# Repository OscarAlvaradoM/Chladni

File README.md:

Proyecto realizado para el congreso nacional de Física 2019.

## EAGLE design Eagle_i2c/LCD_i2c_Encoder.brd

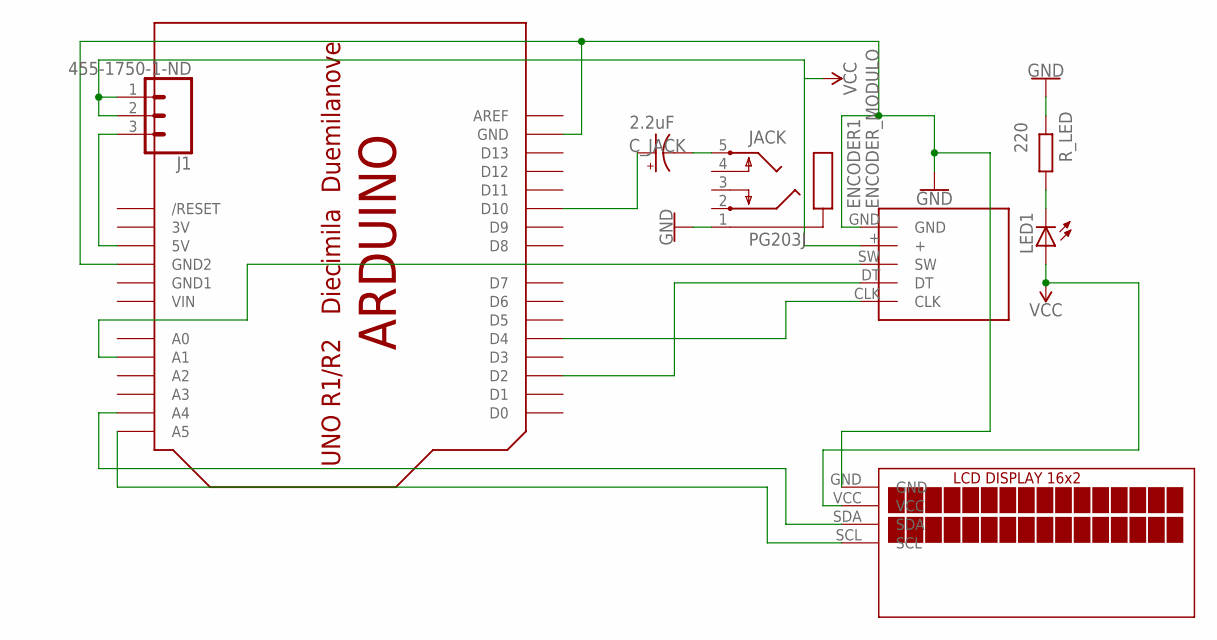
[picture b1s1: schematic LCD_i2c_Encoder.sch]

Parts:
C_JACK: CPOL-USE2,5-6E; E2,5-6E
ENCODER1: ENCODER_MODULO
J1: 455-1750-1-ND; 1X03
JACK: PG203J
LCD1: LCDI2C; TUXGR_16X2_R2
LED1: LED5MM
R_LED: R-EU_0204/7; 0204/7
U$1: ARDUINOUNO; ARDUINO

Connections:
3V: U$1.3V
GND: ENCODER1.GND, JACK.1, LCD1.GND, R_LED.2, U$1.GND, U$1.GND2
GND1: U$1.GND1
unnamed: C_JACK.+, U$1.D10
unnamed: ENCODER1.SW, U$1.A1
unnamed: LED1.K (C), R_LED.1
unnamed: J1.3, U$1.5V
unnamed: C_JACK.-, JACK.5
unnamed: LCD1.SDA, U$1.A4
unnamed: LCD1.SCL, U$1.A5
unnamed: ENCODER1.CLK, U$1.D4
unnamed: ENCODER1.DT, U$1.D2
VCC: ENCODER1.+, J1.1, J1.2, LCD1.VCC, LED1.A
VIN: U$1.VIN

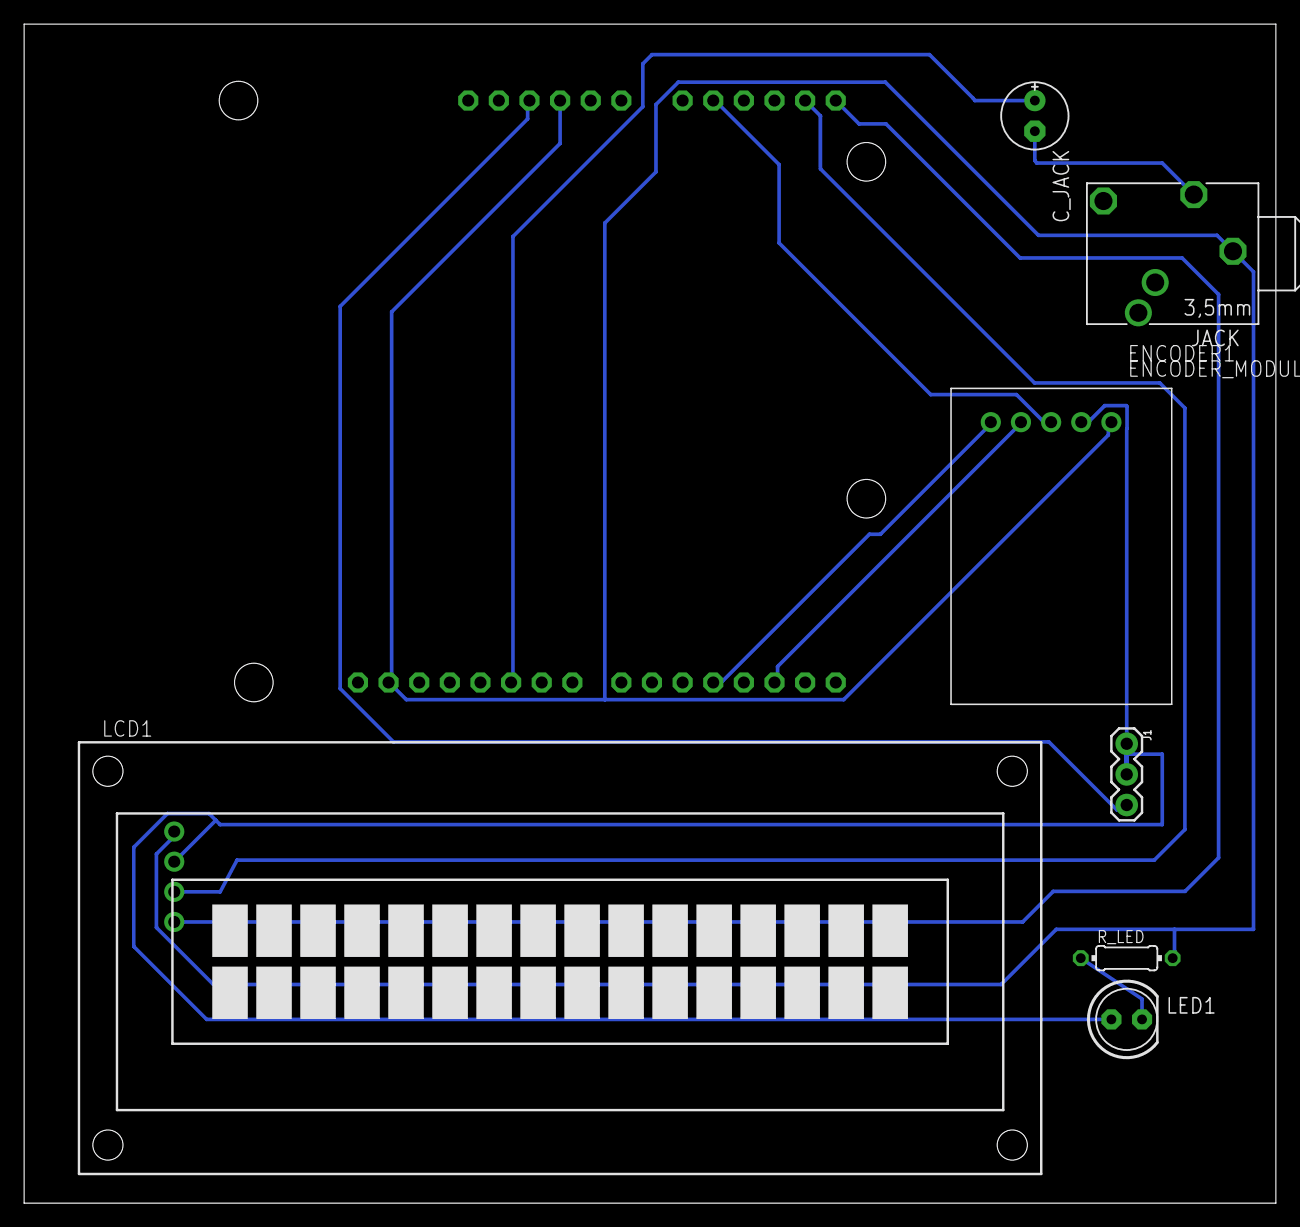
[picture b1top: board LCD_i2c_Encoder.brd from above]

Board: 2 copper layers, 103.8 x 97.8 mm, 8 parts (0 on the bottom side), 11 nets.

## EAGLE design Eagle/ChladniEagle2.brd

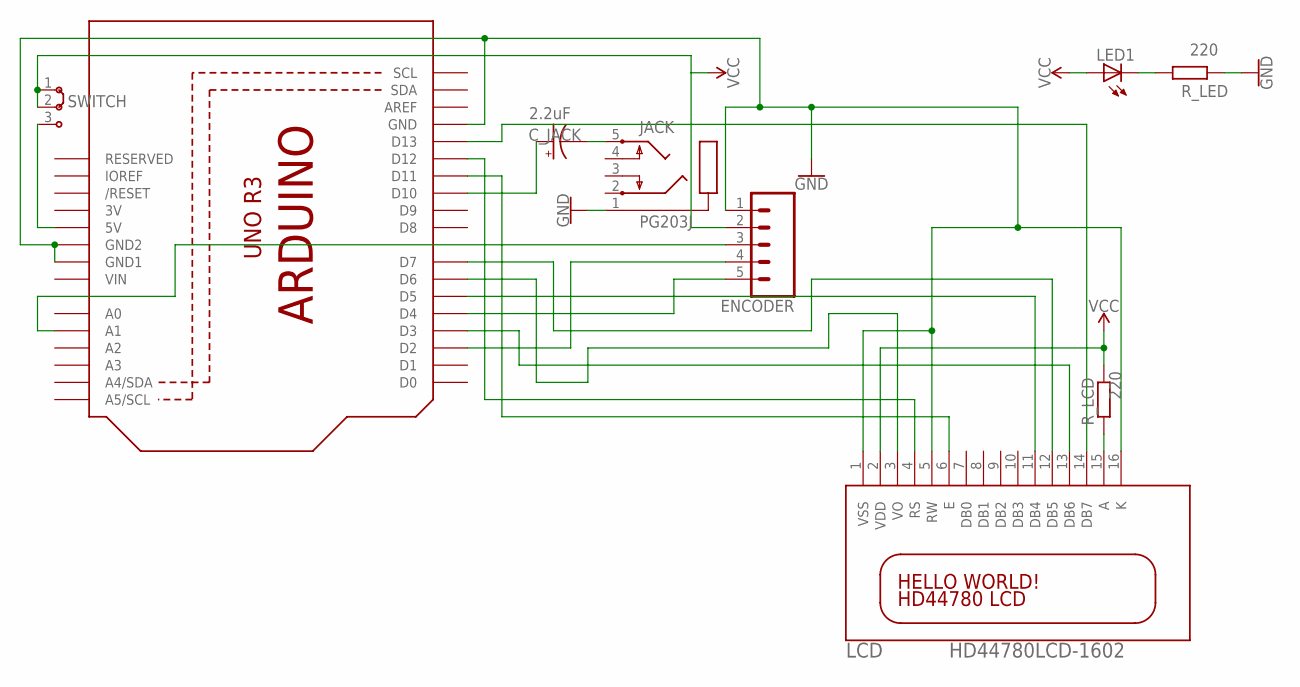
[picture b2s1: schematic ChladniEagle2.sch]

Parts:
C_JACK: CPOL-USE2,5-6E; E2,5-6E
ENCODER: CONN_05NO_SILK; 1X05_NO_SILK
JACK: PG203J
LCD: HD44780LCD-1602; LCD1602
LED1: LED5MM
R_LCD: R-EU_0204/7; 0204/7
R_LED: R-EU_0204/7; 0204/7
SWITCH: J2X2MM; 04C
U1: ARDUINOR3-BPLACE

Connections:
3V: U1.3V
GND: ENCODER.1, JACK.1, LCD.1 (VSS), LCD.5 (RW), LCD.16 (K), R_LED.2, U1.GND, U1.GND1, U1.GND2
unnamed: C_JACK.+, U1.D10
unnamed: ENCODER.3, U1.A1
unnamed: LED1.K (C), R_LED.1
unnamed: SWITCH.3, U1.5V
unnamed: C_JACK.-, JACK.5
unnamed: LCD.15 (A), R_LCD.1
unnamed: LCD.14 (DB7), U1.D13
unnamed: LCD.13 (DB6), U1.D3
unnamed: LCD.12 (DB5), U1.D7
unnamed: LCD.11 (DB4), U1.D5
unnamed: LCD.6 (E), U1.D11
unnamed: LCD.4 (RS), U1.D12
unnamed: LCD.3 (VO), U1.D6
unnamed: ENCODER.5, U1.D4
unnamed: ENCODER.4, U1.D2
VCC: ENCODER.2, LCD.2 (VDD), LED1.A, R_LCD.2, SWITCH.1, SWITCH.2
VIN: U1.VIN

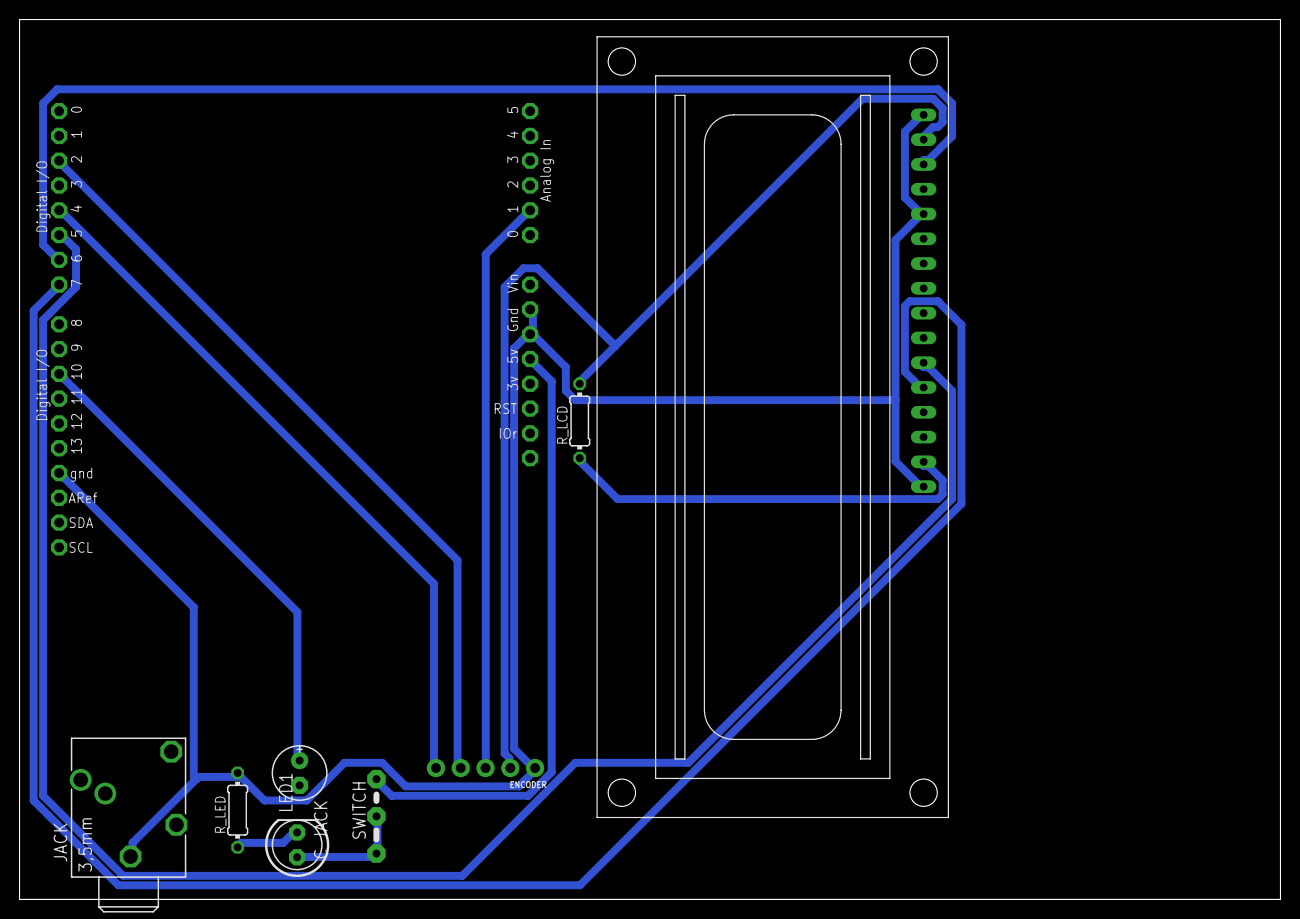
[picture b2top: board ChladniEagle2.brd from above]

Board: 2 copper layers, 129.2 x 90.2 mm, 9 parts (0 on the bottom side), 17 nets.

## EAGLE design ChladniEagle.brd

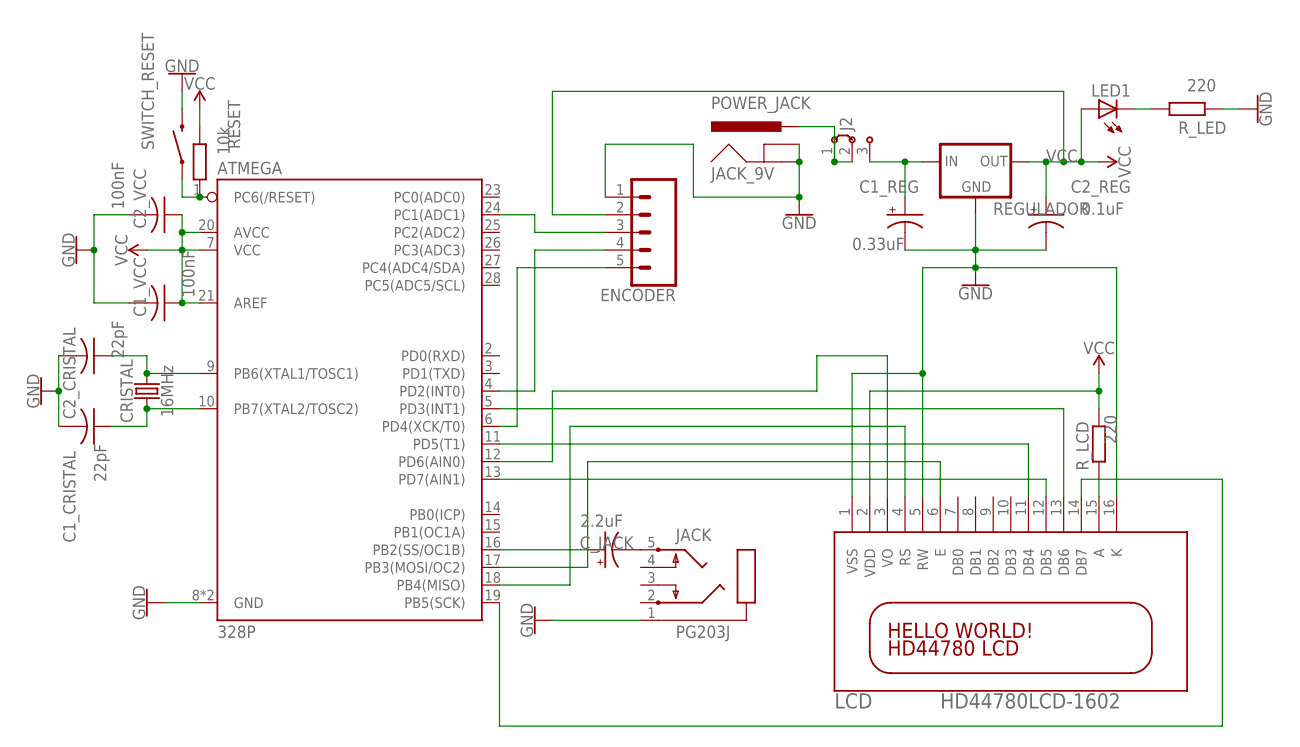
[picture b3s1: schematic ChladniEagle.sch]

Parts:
ATMEGA: 328P; DIP28
C1_CRISTAL, C1_VCC, C2_CRISTAL, C2_VCC: C-US025-024X044; C025-024X044
C1_REG, C2_REG: CPOL-USE2,5-6E; E2,5-6E
CRISTAL: 16MHz; HC49US
C_JACK: CPOL-USE2,5-6E; E2,5-6E
ENCODER: CONN_05NO_SILK; 1X05_NO_SILK
J2: J2X2MM; 04C
JACK: PG203J
JACK_9V: POWER_JACK; POWER_JACK_PTH
LCD: HD44780LCD-1602; LCD1602
LED1: LED5MM
REGULADOR: V_REG_78XX-TO-220; TO-220-ALT
RESET: R-EU_0204/7; 0204/7
R_LCD: R-EU_0204/7; 0204/7
R_LED: R-EU_0204/7; 0204/7
SWITCH_RESET: MOMENTARY-SWITCH-SPST-PTH-6.0MM; TACTILE_SWITCH_PTH_6.0MM

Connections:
GND: ATMEGA.8 (GND), ATMEGA.22 (GND), C1_CRISTAL.2, C1_VCC.2, C2_CRISTAL.2, C2_VCC.2, ENCODER.1, JACK.1, JACK_9V.GND, JACK_9V.GNDBREAK, R_LED.2, SWITCH_RESET.3 (2)
unnamed: C1_REG.+, J2.3, REGULADOR.IN
unnamed: ATMEGA.9 (PB6(XTAL1/TOSC1)), C2_CRISTAL.1, CRISTAL.2
unnamed: ATMEGA.10 (PB7(XTAL2/TOSC2)), C1_CRISTAL.1, CRISTAL.1
unnamed: LED1.K (C), R_LED.1
unnamed: ATMEGA.1 (PC6(/RESET)), RESET.2, SWITCH_RESET.1
unnamed: J2.1, J2.2, JACK_9V.PWR
unnamed: C_JACK.-, JACK.5
unnamed: LCD.15 (A), R_LCD.1
unnamed: ATMEGA.19 (PB5(SCK)), LCD.14 (DB7)
unnamed: ATMEGA.5 (PD3(INT1)), LCD.13 (DB6)
unnamed: ATMEGA.13 (PD7(AIN1)), LCD.12 (DB5)
unnamed: ATMEGA.11 (PD5(T1)), LCD.11 (DB4)
unnamed: ATMEGA.17 (PB3(MOSI/OC2)), LCD.6 (E)
unnamed: ATMEGA.16 (PB2(SS/OC1B)), C_JACK.+
unnamed: ATMEGA.18 (PB4(MISO)), LCD.4 (RS)
unnamed: ATMEGA.12 (PD6(AIN0)), LCD.3 (VO)
unnamed: ATMEGA.6 (PD4(XCK/T0)), ENCODER.5
unnamed: ATMEGA.4 (PD2(INT0)), ENCODER.4
unnamed: ATMEGA.24 (PC1(ADC1)), ENCODER.3
VCC: ATMEGA.7 (VCC), ATMEGA.20 (AVCC), ATMEGA.21 (AREF), C1_VCC.1, C2_REG.+, C2_VCC.1, ENCODER.2, LCD.2 (VDD), LED1.A, REGULADOR.OUT, RESET.1, R_LCD.2
VSS: C1_REG.-, C2_REG.-, LCD.1 (VSS), LCD.5 (RW), LCD.16 (K), REGULADOR.GND

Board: 2 copper layers, 20 parts (0 on the bottom side), 22 nets, no tracks yet.

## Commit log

2019-09-02 Se dañaron los archivos, se recuperan las últimas versiones
2019-09-04 Se cambió a LCD con módulo i2c
2019-09-04 Se pusieron los archivos eagle en una carpeta
2019-09-04 Se creó el esquemático en eagle para la parte de i2c
2019-09-17 Version final circuito Chladni
2019-09-24 Version para imprimir ICAT, Gerbers incluidos
2019-10-04 Lo que se presenta en el congreso

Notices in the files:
parts and their libraries:
SparkFun-IC-Microcontroller: Licensing: Creative Commons ShareAlike 4.0 International - https://creativecommons.org/licenses/by-sa/4.0
